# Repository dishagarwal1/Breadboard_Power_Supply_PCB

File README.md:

# Breadboard Power Supply PCB

This is a KiCad design for a 5V/3.3V breadboard power supply.
Files included:
- KiCad project files
- Schematic
- PCB layout

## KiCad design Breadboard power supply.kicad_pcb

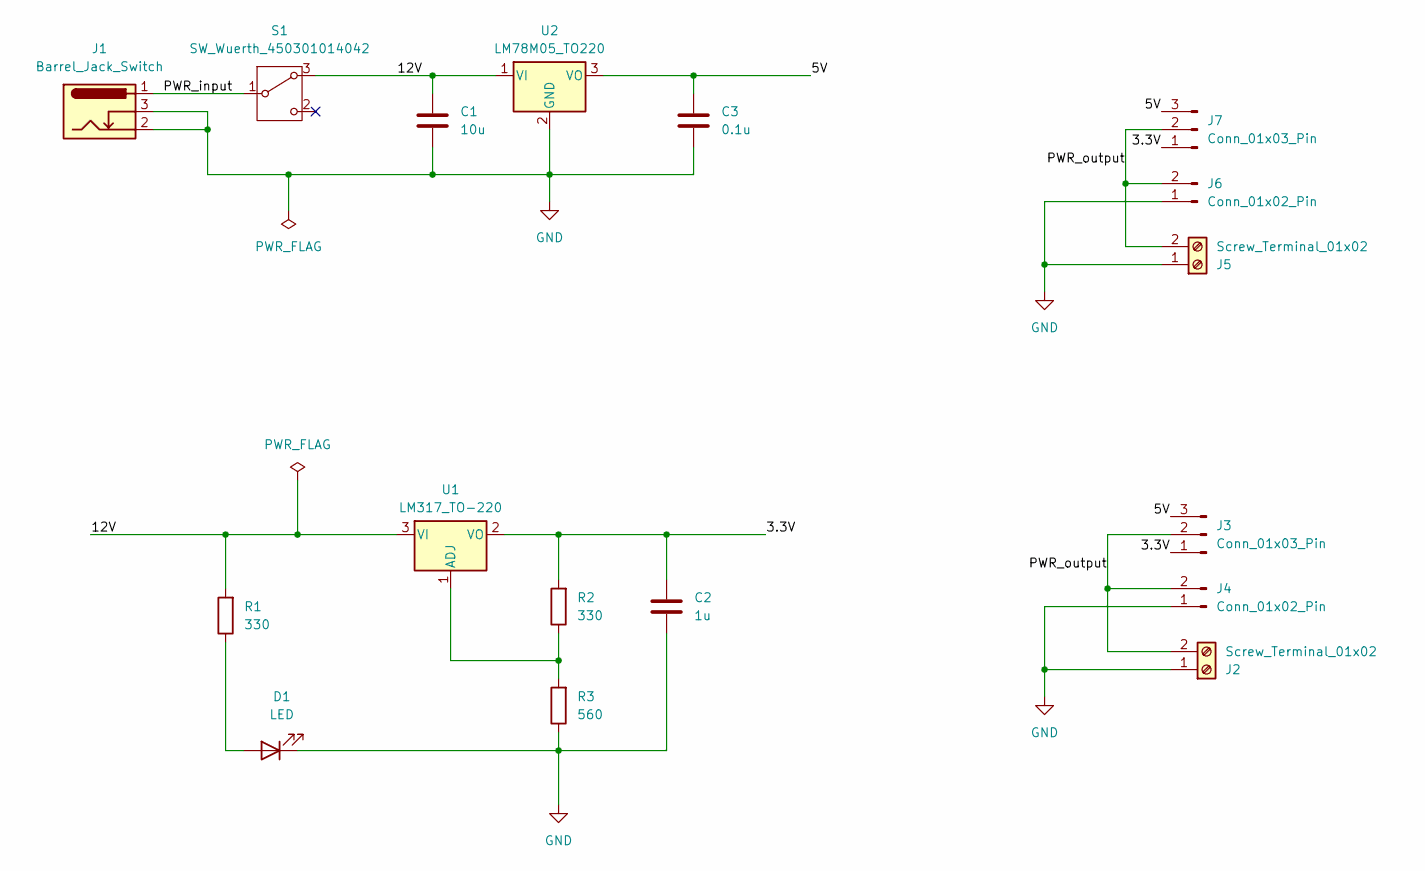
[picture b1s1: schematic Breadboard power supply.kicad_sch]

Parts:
C1: 10u; C_Disc_D3.0mm_W1.6mm_P2.50mm
C2: 1u; C_Disc_D3.0mm_W1.6mm_P2.50mm
C3: 0.1u; C_Disc_D3.0mm_W1.6mm_P2.50mm
D1: LED; LED_D5.0mm
J1: Barrel_Jack_Switch; BarrelJack_Horizontal
J2, J5: Screw_Terminal_01x02; TerminalBlock_MaiXu_MX126-5.0-02P_1x02_P5.00mm
J3, J7: Conn_01x03_Pin; PinHeader_1x03_P2.54mm_Vertical
J4, J6: Conn_01x02_Pin; PinHeader_1x02_P2.54mm_Vertical
R1, R2: 330; R_Axial_DIN0204_L3.6mm_D1.6mm_P7.62mm_Horizontal
R3: 560; R_Axial_DIN0204_L3.6mm_D1.6mm_P7.62mm_Horizontal
S1: SW_Wuerth_450301014042; SW_Slide-03_Wuerth-WS-SLTV_10x2.5x6.4_P2.54mm
U1: LM317_TO-220; TO-220-3_Vertical
U2: LM78M05_TO220; TO-220-3_Vertical

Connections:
/3.3V: C2.1, J3.1, J7.1, R2.2, U1.2 (VO)
/5V: C3.1, J3.3, J7.3, U2.3 (VO)
/12V: C1.1, R1.2, S1.3 (A), U1.3 (VI), U2.1 (VI)
/PWR_input: J1.1, S1.1 (B)
/PWR_output: J2.2, J3.2, J4.2, J5.2, J6.2, J7.2
GND: C1.2, C2.2, C3.2, D1.1 (K), J1.2, J1.3, J2.1, J4.1, J5.1, J6.1, R3.1, U2.2 (GND)
unnamed: D1.2 (A), R1.1
unnamed: R2.1, R3.2, U1.1 (ADJ)

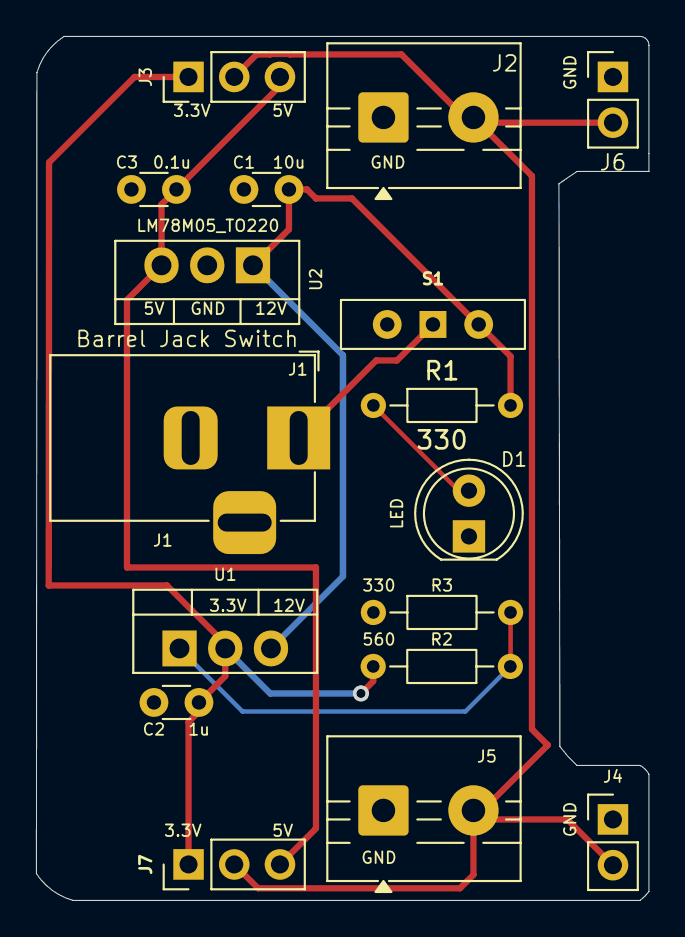
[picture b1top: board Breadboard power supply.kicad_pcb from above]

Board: 2 copper layers, 34.0 x 48.0 mm, 17 parts (0 on the bottom side), 8 nets.

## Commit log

2026-01-18 Add README for breadboard power supply PCB project
